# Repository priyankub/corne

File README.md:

# Corne Chocolate Wireless

A modern, low-profile split ergonomic keyboard based on the Corne (crkbd) Chocolate v2.1 footprint. Designed for completely wireless operation with **nice!nano v2**, native **5-pin nice!view (Sharp Memory LCD)** support, onboard power management, and RGB backlighting.

---

## Key Features

* **Low-Profile Choc v1**: Kailh Choc PG1350 switches with hotswap sockets.
* **Native nice!view Header**: 5-pin pinout tailored specifically for nice!view and Sharp Memory LCD modules (`[CS, MOSI, SCK, VCC, GND]`) without adapter boards or bodge wires.
* **Dedicated Power Control**: Onboard slide power switch (PCM12) and 2-pin JST-PH 2.0mm LiPo battery connector routing power directly to the controller's `RAW` pin.
* **RGB Matrix & Underglow**: 27× SK6812MINI LEDs per side (6 underglow + 21 per-key).
  - WS2812 data line routed to **Pin 2 (P0.08 / D0)** to dedicate **Pin 1 (P0.06 / D1)** to the display Chip Select (`CS`).
* **Reversible PCB**: A single reversible PCB design is flipped for either the left or right hand.
* **ZMK Firmware Ready**: Complete ZMK configuration, keymap, and GitHub Actions build workflow included out of the box.

---

## Hardware Specifications & Pinout

### Microcontroller (nice!nano v2 / nRF52840)

| Signal | nice!nano Pin | nRF Pin | Function |
|:---|:---:|:---:|:---|
| **CS** | 1 (TX0 / D1) | `P0.06` | Display Chip Select |
| **LED** | 2 (RX1 / D0) | `P0.08` | WS2812 RGB Data |
| **SDA / MOSI** | 3 (D2) | `P0.17` | Display MOSI / I2C SDA |
| **SCL / SCK** | 4 (D3) | `P0.20` | Display SCK / I2C SCL |
| **RAW** | 24 | — | Battery positive (switched via power slide switch) |

### 5-Pin Display Connector Pinout

Viewed from the front (component side) with header pins at the bottom:

```text
Pin:    [ 1 ]      [ 2 ]      [ 3 ]      [ 4 ]      [ 5 ]
Signal:  CS        MOSI       SCK        VCC        GND
        (P0.06)    (P0.17)    (P0.20)   (3.3V)
```

---

## Assembly & Solder Jumpers

Because the PCB is reversible, you bridge the **5 solder jumpers** on the **top (active) side** of each half to route the display signals:

* **Left Hand (Top / Front side facing up)**:
  Solder jumpers **`JP1` through `JP5`** on the front layer (`F.Cu`).
  * `JP5` $\rightarrow$ Pin 1 (`CS`)
  * `JP4` $\rightarrow$ Pin 2 (`MOSI / SDA`)
  * `JP3` $\rightarrow$ Pin 3 (`SCK / SCL`)
  * `JP2` $\rightarrow$ Pin 4 (`VCC`)
  * `JP1` $\rightarrow$ Pin 5 (`GND`)

* **Right Hand (Bottom / Back side facing up)**:
  Solder jumpers **`JP6` through `JP10`** on the back layer (`B.Cu`).
  * `JP6` $\rightarrow$ Pin 1 (`CS`)
  * `JP7` $\rightarrow$ Pin 2 (`MOSI / SDA`)
  * `JP8` $\rightarrow$ Pin 3 (`SCK / SCL`)
  * `JP9` $\rightarrow$ Pin 4 (`VCC`)
  * `JP10` $\rightarrow$ Pin 5 (`GND`)

> [!TIP]
> Only solder the jumpers on the top side of each half. Leave the jumpers on the underside unbridged.

---

## Fabrication & Ordering

Ready-to-manufacture files are located in [`hardware/production/`](hardware/production/):

| File | Description |
|:---|:---|
| [`Corne_Chocolate_2.1.zip`](hardware/production/Corne_Chocolate_2.1.zip) | Complete Gerber & Drill archive (JLCPCB / PCBWay ready) |
| [`bom.csv`](hardware/production/bom.csv) | Bill of Materials with footprint designators |
| [`positions.csv`](hardware/production/positions.csv) | Pick & Place (CPL) component coordinates |
| [`netlist.ipc`](hardware/production/netlist.ipc) | IPC-D-356 electrical test netlist |

### Recommended Fab Settings (JLCPCB)
* **Base Material**: FR-4 (1.6mm thickness or 1.2mm for ultra-low profile)
* **Layers**: 2 layers
* **Surface Finish**: ENIG (recommended for hotswap durability) or HASL Lead-Free
* **Silkscreen**: Black PCB with white silkscreen (or standard preferences)
* **Castellated Holes**: No

---

## Firmware (ZMK)

The repository includes a battle-tested ZMK setup under [`firmware/`](firmware/):

* **Custom SPI Pinctrl**: Configures `P0.08` for the WS2812 LED chain, preserving `P0.06` for display `CS`.
* **Sleep & Power Management**: Deep sleep timeout set to 30 minutes with soft-off support.
* **ZMK Studio**: Enabled for real-time keymap remapping without reflashing.

### Building Firmware
Build using the included GitHub Actions workflow or locally with the ZMK toolchain:
```bash
west build -b nice_nano//zmk -d build/left -- -DSHIELD="corne_left nice_view_adapter nice_epaper"
west build -b nice_nano//zmk -d build/right -- -DSHIELD="corne_right nice_view_adapter nice_epaper"
```

---

## Repository Layout

```text
.
├── hardware/                  # KiCad 9 PCB and Schematic source files
│   ├── corne-chocolate.kicad_pro
│   ├── corne-chocolate.kicad_sch
│   ├── corne-chocolate.kicad_pcb
│   ├── corne-chocolate.step
│   ├── kbd/                   # KiCad symbol & footprint libraries
│   └── production/            # Gerbers, Drill, BOM, and CPL files
└── firmware/                  # ZMK configuration & build recipes
    ├── config/                # corne.keymap and corne.conf
    └── build.yaml             # GitHub Actions matrix configuration
```

---

<details>
<summary><b>Note for Prototype (First Batch) Builders</b></summary>

If you are working with an early prototype PCB printed before September 2026 (which had the display header signals routed in reverse order), you can run thin enamel jumper wires across the solder pads on the front of the left half instead of reprinting:
- `JP5 Pad 2` (Screen Pin 1 / CS) $\rightarrow$ Wire to `JP1 Pad 1`
- `JP4 Pad 2` (Screen Pin 2 / MOSI) $\rightarrow$ Wire to `JP5 Pad 1`
- `JP3 Pad 2` (Screen Pin 3 / SCK) $\rightarrow$ Wire to `JP4 Pad 1`
- `JP2 Pad 2` (Screen Pin 4 / VCC) $\rightarrow$ Wire to `JP3 Pad 1`
- `JP1 Pad 2` (Screen Pin 5 / GND) $\rightarrow$ Wire to `JP2 Pad 1`

*The files currently in this repository have this issue resolved natively in copper.*
</details>

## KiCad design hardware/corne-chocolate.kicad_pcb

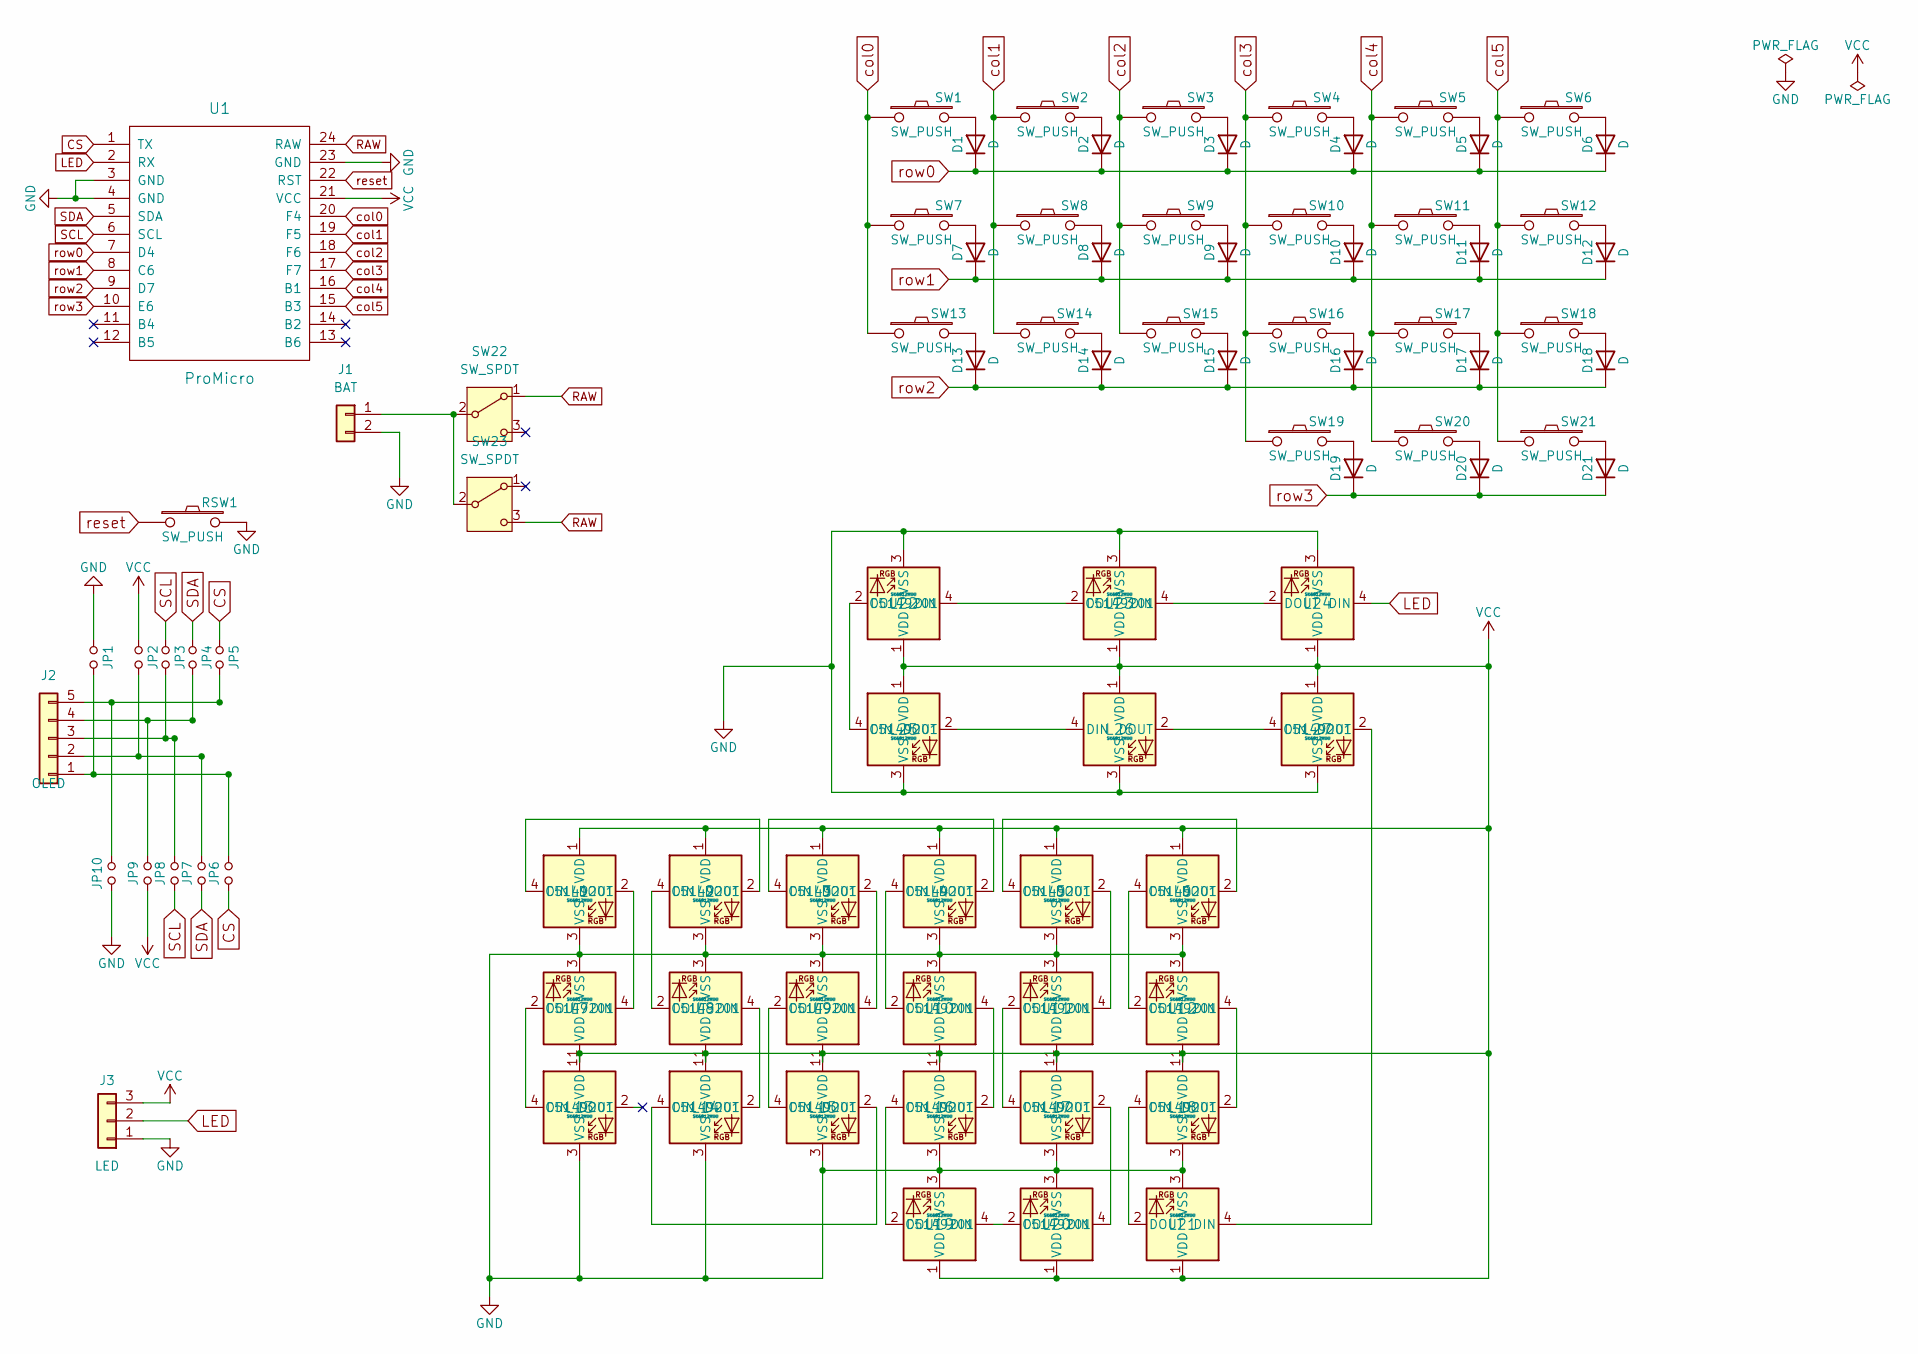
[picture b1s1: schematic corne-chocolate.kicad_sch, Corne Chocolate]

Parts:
D1, D2, D3, D4, D5, D6, D7, D8, D9, D10, D11, D12, D13, D14, D15, D16, D17, D18, D19, D20, D21: D; D3_TH_SMD
J1: BAT; JST_PH_S2B-PH-K_1x02_P2.00mm_Horizontal
J2: OLED; PinSocket_1x05_P2.54mm_Vertical
J3: LED; StripLED_rev
JP1, JP2, JP3, JP4, JP5, JP6, JP7, JP8, JP9, JP10: Jumper
L1, L2, L3, L4, L5, L6, L7, L8, L9, L10, L11, L12, L13, L14, L15, L16, L17, L18, L19, L20, L21, L22, L23, L24, L25, L26, L27: SK6812MINI; LED_SK6812MINI; LCSC C5149201
RSW1: SW_PUSH; ResetSW
SW1, SW2, SW3, SW4, SW5, SW6, SW7, SW8, SW9, SW10, SW11, SW12, SW13, SW14, SW15, SW16, SW17, SW18, SW19, SW20: SW_PUSH; Choc_Hotswap
SW21: SW_PUSH; Choc_Hotswap_1.5u
SW22, SW23: SW_SPDT; SW_SPDT_PCM12
U1: ProMicro; ProMicro_v2

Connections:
CS: JP5.1, JP6.1, U1.1 (TX)
GND: J1.2, J3.1, JP1.1, JP10.1, L1.3 (VSS), L2.3 (VSS), L3.3 (VSS), L4.3 (VSS), L5.3 (VSS), L6.3 (VSS), L7.3 (VSS), L8.3 (VSS), L9.3 (VSS), L10.3 (VSS), L11.3 (VSS), L12.3 (VSS), L13.3 (VSS), L14.3 (VSS), L15.3 (VSS), L16.3 (VSS), L17.3 (VSS), L18.3 (VSS), L19.3 (VSS), L20.3 (VSS), L21.3 (VSS), L22.3 (VSS), L23.3 (VSS), L24.3 (VSS), L25.3 (VSS), L26.3 (VSS), L27.3 (VSS), RSW1.2, U1.3 (GND), U1.4 (GND), U1.23 (GND); also elsewhere on the board
LED: J3.2, L24.4 (DIN), U1.2 (RX); also elsewhere on the board
unnamed: D1.2 (A), SW1.2
unnamed: D2.2 (A), SW2.2
unnamed: D3.2 (A), SW3.2
unnamed: D4.2 (A), SW4.2
unnamed: D5.2 (A), SW5.2
unnamed: D6.2 (A), SW6.2
unnamed: D7.2 (A), SW7.2
unnamed: D8.2 (A), SW8.2
unnamed: D9.2 (A), SW9.2
unnamed: D10.2 (A), SW10.2
unnamed: D11.2 (A), SW11.2
unnamed: D12.2 (A), SW12.2
unnamed: D13.2 (A), SW13.2
unnamed: D14.2 (A), SW14.2
unnamed: D15.2 (A), SW15.2
unnamed: D16.2 (A), SW16.2
unnamed: D17.2 (A), SW17.2
unnamed: D18.2 (A), SW18.2
unnamed: D19.2 (A), SW19.2
unnamed: D20.2 (A), SW20.2
unnamed: D21.2 (A), SW21.2
unnamed 24: J1.1, SW22.2 (B), SW23.2 (B); also elsewhere on the board
unnamed: J2.1, JP1.2, JP6.2
unnamed: J2.2, JP2.2, JP7.2
unnamed: J2.3, JP3.2, JP8.2
unnamed: J2.4, JP4.2, JP9.2
unnamed: J2.5, JP5.2, JP10.2
unnamed: L1.4 (DIN), L2.2 (DOUT)
unnamed: L1.2 (DOUT), L7.4 (DIN)
unnamed: L2.4 (DIN), L8.2 (DOUT)
unnamed: L3.4 (DIN), L4.2 (DOUT)
unnamed: L3.2 (DOUT), L9.4 (DIN)
unnamed: L5.4 (DIN), L6.2 (DOUT)
unnamed: L10.4 (DIN), L16.2 (DOUT)
unnamed: L4.4 (DIN), L10.2 (DOUT)
unnamed: L5.2 (DOUT), L11.4 (DIN)
unnamed: L11.2 (DOUT), L17.4 (DIN)
unnamed: L12.4 (DIN), L18.2 (DOUT)
unnamed: L6.4 (DIN), L12.2 (DOUT)
unnamed: L7.2 (DOUT), L13.4 (DIN)
unnamed: L14.4 (DIN), L15.2 (DOUT)
unnamed: L8.4 (DIN), L14.2 (DOUT)
unnamed: L9.2 (DOUT), L15.4 (DIN)
unnamed: L16.4 (DIN), L19.2 (DOUT)
unnamed: L17.2 (DOUT), L20.4 (DIN)
unnamed: L18.4 (DIN), L21.2 (DOUT)
unnamed: L19.4 (DIN), L20.2 (DOUT)
unnamed 50: L21.4 (DIN), L27.2 (DOUT); also elsewhere on the board
unnamed 51: L22.4 (DIN), L23.2 (DOUT); also elsewhere on the board
unnamed 52: L22.2 (DOUT), L25.4 (DIN); also elsewhere on the board
unnamed 53: L23.4 (DIN), L24.2 (DOUT); also elsewhere on the board
unnamed 54: L25.2 (DOUT), L26.4 (DIN); also elsewhere on the board
unnamed 55: L26.2 (DOUT), L27.4 (DIN); also elsewhere on the board
RAW: SW22.1 (A), SW23.3 (C), U1.24 (RAW)
SCL: JP3.1, JP8.1, U1.6 (SCL)
SDA: JP4.1, JP7.1, U1.5 (SDA)
VCC: J3.3, JP2.1, JP9.1, L1.1 (VDD), L2.1 (VDD), L3.1 (VDD), L4.1 (VDD), L5.1 (VDD), L6.1 (VDD), L7.1 (VDD), L8.1 (VDD), L9.1 (VDD), L10.1 (VDD), L11.1 (VDD), L12.1 (VDD), L13.1 (VDD), L14.1 (VDD), L15.1 (VDD), L16.1 (VDD), L17.1 (VDD), L18.1 (VDD), L19.1 (VDD), L20.1 (VDD), L21.1 (VDD), L22.1 (VDD), L23.1 (VDD), L24.1 (VDD), L25.1 (VDD), L26.1 (VDD), L27.1 (VDD), U1.21 (VCC); also elsewhere on the board
col0: SW1.1, SW7.1, SW13.1, U1.20 (F4)
col1: SW2.1, SW8.1, SW14.1, U1.19 (F5)
col2: SW3.1, SW9.1, SW15.1, U1.18 (F6)
col3: SW4.1, SW10.1, SW16.1, SW19.1, U1.17 (F7)
col4: SW5.1, SW11.1, SW17.1, SW20.1, U1.16 (B1)
col5: SW6.1, SW12.1, SW18.1, SW21.1, U1.15 (B3)
reset: RSW1.1, U1.22 (RST)
row0: D1.1 (K), D2.1 (K), D3.1 (K), D4.1 (K), D5.1 (K), D6.1 (K), U1.7 (D4)
row1: D7.1 (K), D8.1 (K), D9.1 (K), D10.1 (K), D11.1 (K), D12.1 (K), U1.8 (C6)
row2: D13.1 (K), D14.1 (K), D15.1 (K), D16.1 (K), D17.1 (K), D18.1 (K), U1.9 (D7)
row3: D19.1 (K), D20.1 (K), D21.1 (K), U1.10 (E6)

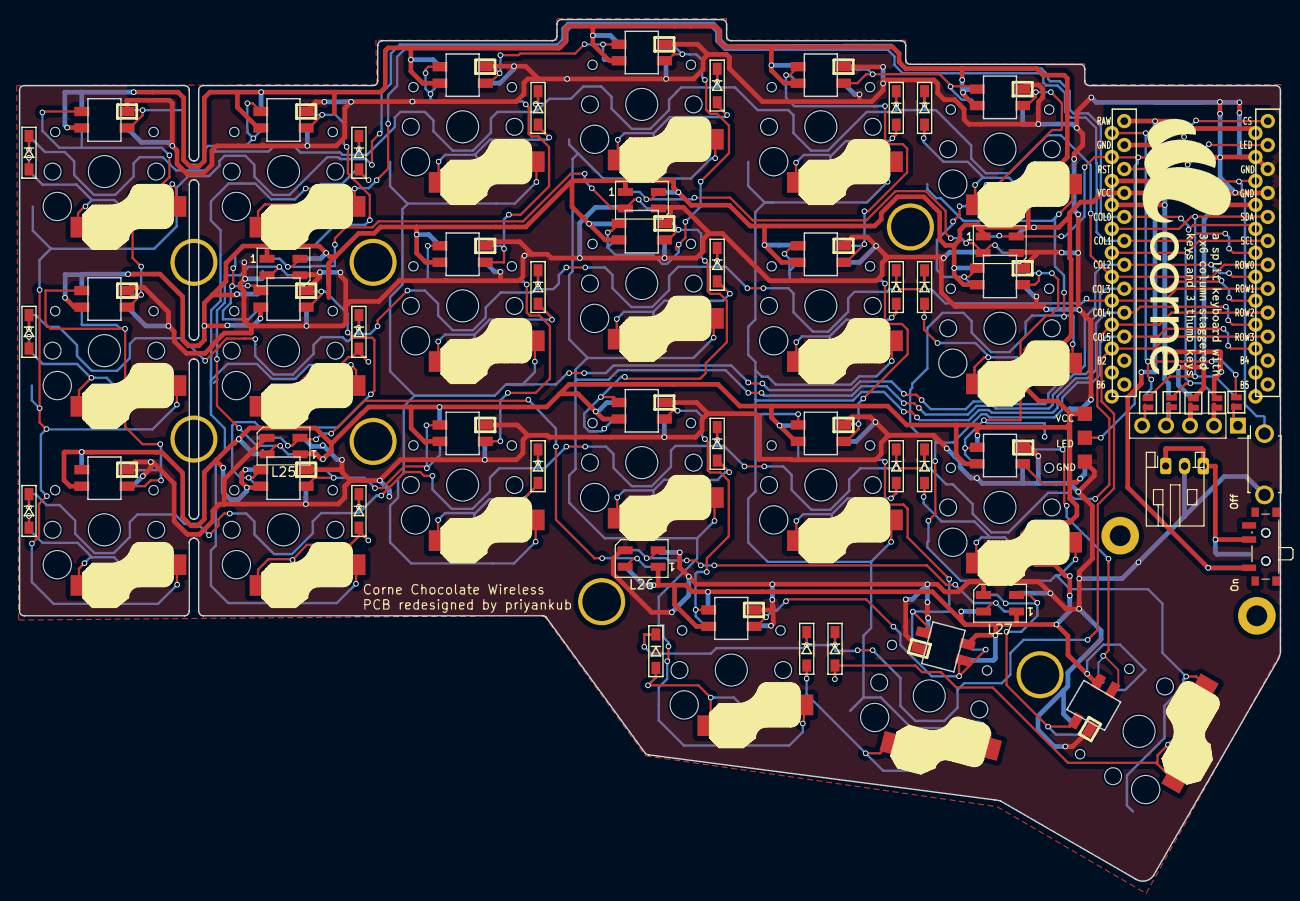
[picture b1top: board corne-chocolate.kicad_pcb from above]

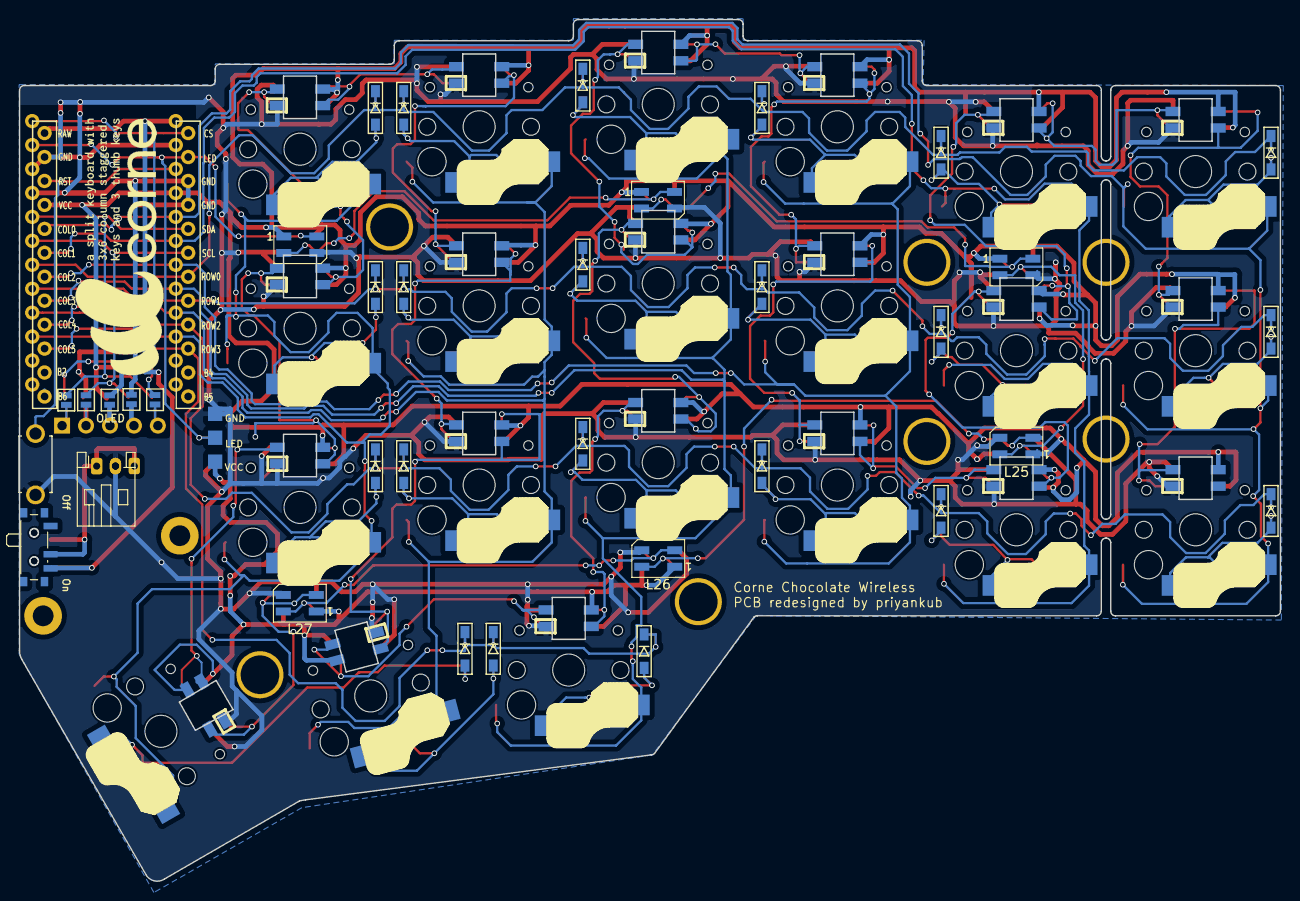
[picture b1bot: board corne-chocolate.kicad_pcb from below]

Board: 2 copper layers, 133.8 x 91.4 mm, 93 parts (14 on the bottom side), 71 nets.

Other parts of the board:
J1#2: BAT; JST_PH_S2B-PH-K_1x02_P2.00mm_Horizontal
L22#2, L23#2, L24#2, L25#2, L26#2, L27#2: SK6812MINI; LED_SK6812MINI_PLCC4_3.5x3.5mm_P1.75mm

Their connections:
GND: J1#2.2, L22#2.3 (VSS), L23#2.3 (VSS), L24#2.3 (VSS), L25#2.3 (VSS), L26#2.3 (VSS), L27#2.3 (VSS); also elsewhere on the board
LED: L24#2.4 (DIN); also elsewhere on the board
unnamed 24: J1#2.1; also elsewhere on the board
unnamed 50: L27#2.2 (DOUT); also elsewhere on the board
unnamed 51: L22#2.4 (DIN), L23#2.2 (DOUT); also elsewhere on the board
unnamed 52: L22#2.2 (DOUT), L25#2.4 (DIN); also elsewhere on the board
unnamed 53: L23#2.4 (DIN), L24#2.2 (DOUT); also elsewhere on the board
unnamed 54: L25#2.2 (DOUT), L26#2.4 (DIN); also elsewhere on the board
unnamed 55: L26#2.2 (DOUT), L27#2.4 (DIN); also elsewhere on the board
VCC: L22#2.1 (VDD), L23#2.1 (VDD), L24#2.1 (VDD), L25#2.1 (VDD), L26#2.1 (VDD), L27#2.1 (VDD); also elsewhere on the board

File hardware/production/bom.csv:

Designator,Footprint,Quantity,Value,LCSC Part #
"D1, D10, D11, D12, D13, D14, D15, D16, D17, D18, D19, D2, D20, D21, D3, D4, D5, D6, D7, D8, D9",D3_SMD,21,D,
"J1_2, J1",JST_PH_S2B-PH-K_1x02_P2.00mm_Horizontal,2,BAT,
"J2, J4",PinSocket_1x05_P2.54mm_Vertical,2,OLED,
J3,StripLED_rev,1,LED,
"JP1, JP10, JP2, JP3, JP4, JP5, JP6, JP7, JP8, JP9",Jumper,10,~,
"L1, L10, L11, L12, L13, L14, L15, L16, L17, L18, L19, L2, L20, L21, L3, L4, L5, L6, L7, L8, L9",SK6812MINI_rev,21,SK6812MINI,C5149201
"L22_2, L22, L23_2, L23, L24_2, L24, L25_2, L25, L26_2, L26, L27_2, L27",LED_SK6812MINI_PLCC4_3.5x3.5mm_P1.75mm,12,SK6812MINI,C5149201
RSW1,ResetSW,1,SW_PUSH,
"SW1, SW10, SW11, SW12, SW13, SW14, SW15, SW16, SW17, SW18, SW19, SW2, SW20, SW3, SW4, SW5, SW6, SW7, SW8, SW9",Choc_Hotswap,20,SW_PUSH,
SW21,Choc_Hotswap_1.5u,1,SW_PUSH,
"SW22, SW23",SW_SPDT_PCM12,2,SW_SPDT,
U1,ProMicro_v2,1,ProMicro,
